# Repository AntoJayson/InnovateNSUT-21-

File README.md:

# InnovateNSUT-21-
InnovateNSUT 21'  Codes

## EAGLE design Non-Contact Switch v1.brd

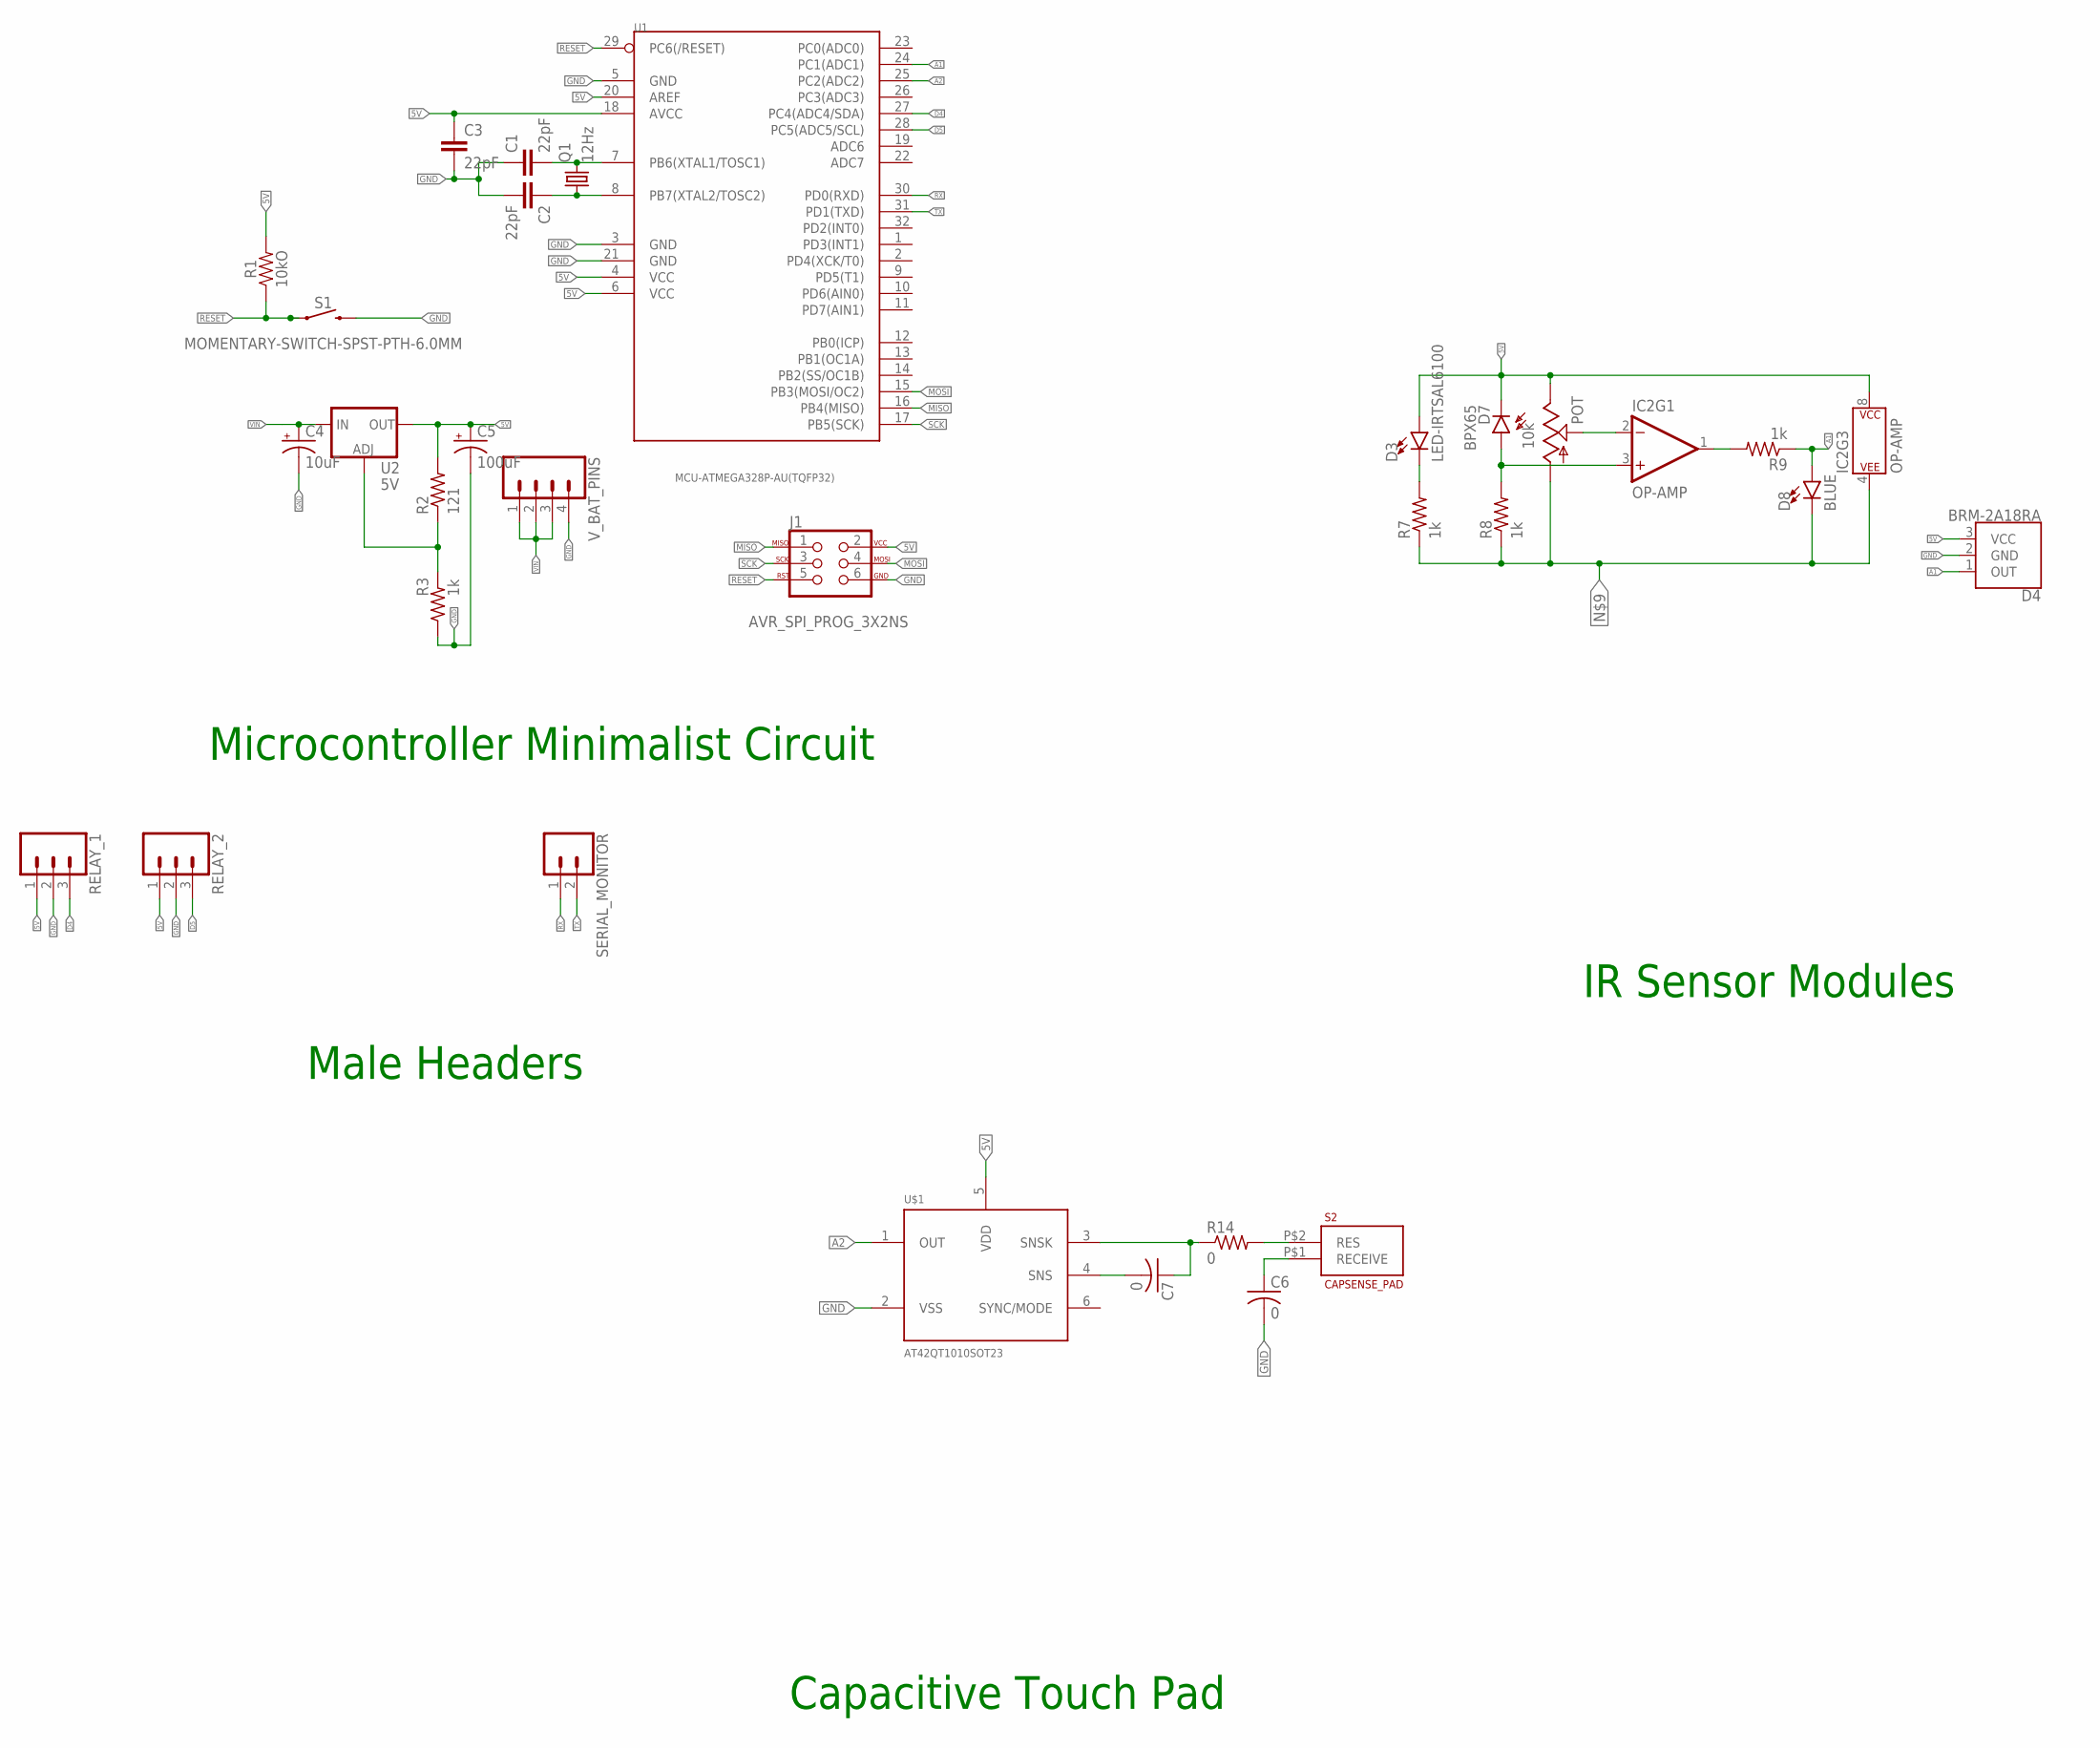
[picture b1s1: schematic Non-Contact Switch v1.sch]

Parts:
C1, C2, C3: 22pF; C0603
C4: 10uF; 0603-POLAR
C5: 100uF; 0603-POLAR
C6, C7: 0; C0603K
D3: LED-IRTSAL6100; LED_5MM
D4: BRM-2A18RA; BRM-2508
D7: BPX65
D8: BLUE; LED-0603
IC2: OP-AMP; SO08
J1: AVR_SPI_PROG_3X2NS; 2X3-NS
POT: 10k; PT-10
Q1: 12Hz; HC49UP
R1: 10kO; 0603
R2: 121; R0603
R3, R7, R8, R9: 1k; R0603
R14: 0; R0603
RELAY_1, RELAY_2: CONN_031X03_NO_SILK; 1X03_NO_SILK
S1: MOMENTARY-SWITCH-SPST-PTH-6.0MM; TACTILE_SWITCH_PTH_6.0MM
S2: CAPSENSE_PAD
SERIAL_MONITOR: CONN_02; 1X02
U1: MCU-ATMEGA328P-AU(TQFP32); TQFP32-0.8-7X7MM
U2: 5V; SOT223
U$1: AT42QT1010SOT23; SOT23-6
V_BAT_PINS: CONN_04LOCK; 1X04_LOCK

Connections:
5V: C3.1, C5.+, D3.A, D4.3 (VCC), D7.K (C), IC2.8 (P$V+), J1.2, POT.E, R1.2, R2.2, RELAY_1.1, RELAY_2.1, U1.4 (VCC), U1.6 (VCC), U1.18 (AVCC), U1.20 (AREF), U2.2 (OUT), U2.4 (OUT), U$1.5 (VDD)
A1: D4.1 (OUT), D8.A, R9.1, U1.24 (PC1(ADC1))
A2: U1.25 (PC2(ADC2)), U$1.1 (OUT)
D4: RELAY_1.3, U1.27 (PC4(ADC4/SDA))
D5: RELAY_2.3, U1.28 (PC5(ADC5/SCL))
GND: C1.1, C2.2, C3.2, C4.-, C5.-, C6.2, D4.2 (GND), IC2.2 (-IN), J1.6, POT.S, R3.1, RELAY_1.2, RELAY_2.2, S1.3 (2), U1.3 (GND), U1.5 (GND), U1.21 (GND), U$1.2 (VSS), V_BAT_PINS.4
MISO: J1.1, U1.16 (PB4(MISO))
MOSI: J1.4, U1.15 (PB3(MOSI/OC2))
unnamed: C1.2, Q1.2, U1.7 (PB6(XTAL1/TOSC1))
unnamed: C2.1, Q1.1, U1.8 (PB7(XTAL2/TOSC2))
unnamed: C6.1, S2.P$1 (RECEIVE)
unnamed: D7.A, IC2.3 (+IN), R8.2
unnamed: D3.K (C), R7.2
unnamed: IC2.1 (OUT), R9.2
unnamed: R2.1, R3.2, U2.1 (ADJ)
unnamed: D8.C, IC2.4 (P$V-), POT.A, R7.1, R8.1
unnamed: R14.2, S2.P$2 (RES)
unnamed: C7.1, R14.1, U$1.3 (SNSK)
unnamed: C7.2, U$1.4 (SNS)
RESET: J1.5, R1.1, S1.1, U1.29 (PC6(/RESET))
RX: SERIAL_MONITOR.1, U1.30 (PD0(RXD))
SCK: J1.3, U1.17 (PB5(SCK))
TX: SERIAL_MONITOR.2, U1.31 (PD1(TXD))
VIN: C4.+, U2.3 (IN), V_BAT_PINS.1, V_BAT_PINS.2, V_BAT_PINS.3

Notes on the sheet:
Microcontroller Minimalist Circuit
IR Sensor Modules
Male Headers
Capacitive Touch Pad

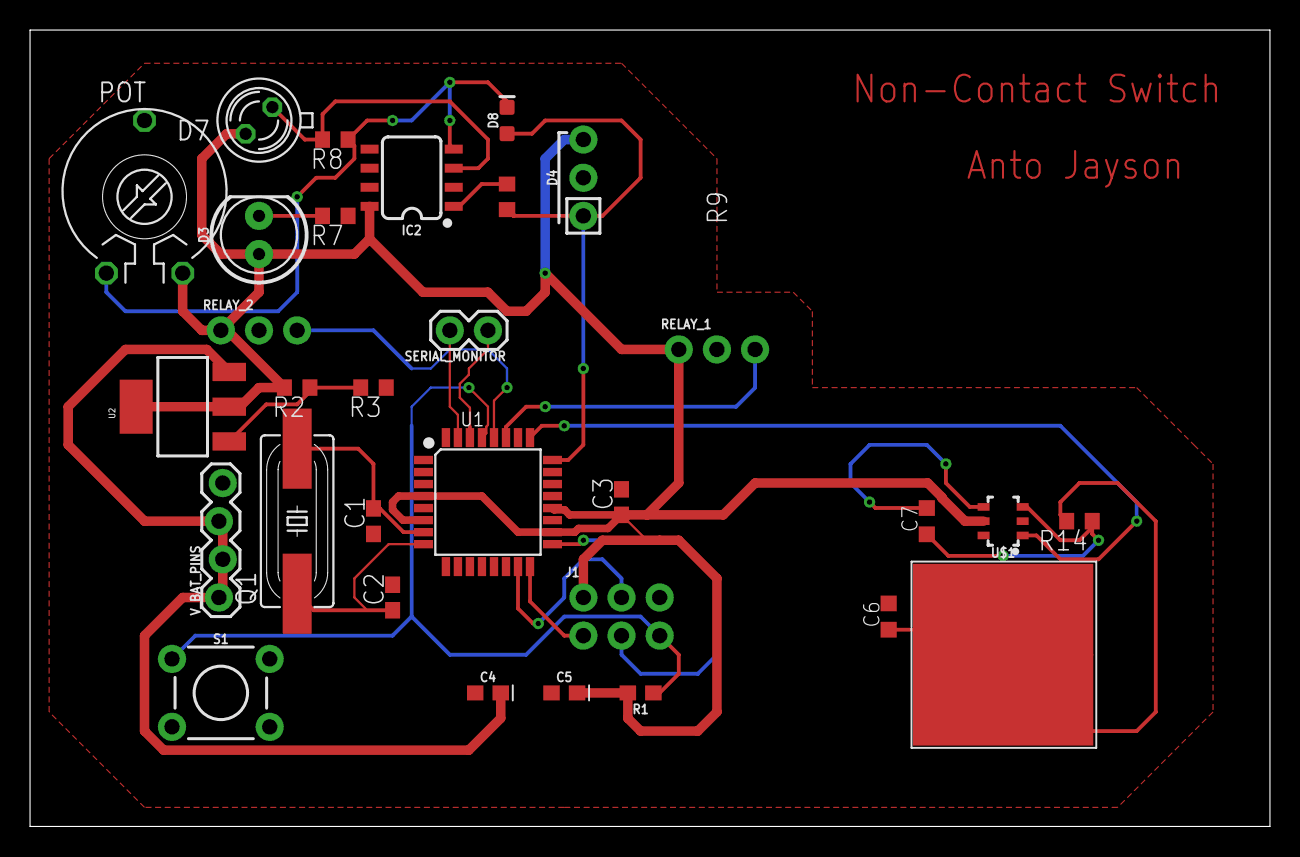
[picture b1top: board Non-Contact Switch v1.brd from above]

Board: 2 copper layers, 82.5 x 53.0 mm, 31 parts (0 on the bottom side), 24 nets.

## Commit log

2021-03-09 Create Proxy detector using voice recognition
2021-03-09 Create Face mask detector
2021-03-09 Update Face mask detector
2021-03-10 Update Proxy detector using voice recognition

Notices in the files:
parts and their libraries:
SparkFun-Capacitors: Licensing: Creative Commons ShareAlike 4.0 International - https://creativecommons.org/licenses/by-sa/4.0
